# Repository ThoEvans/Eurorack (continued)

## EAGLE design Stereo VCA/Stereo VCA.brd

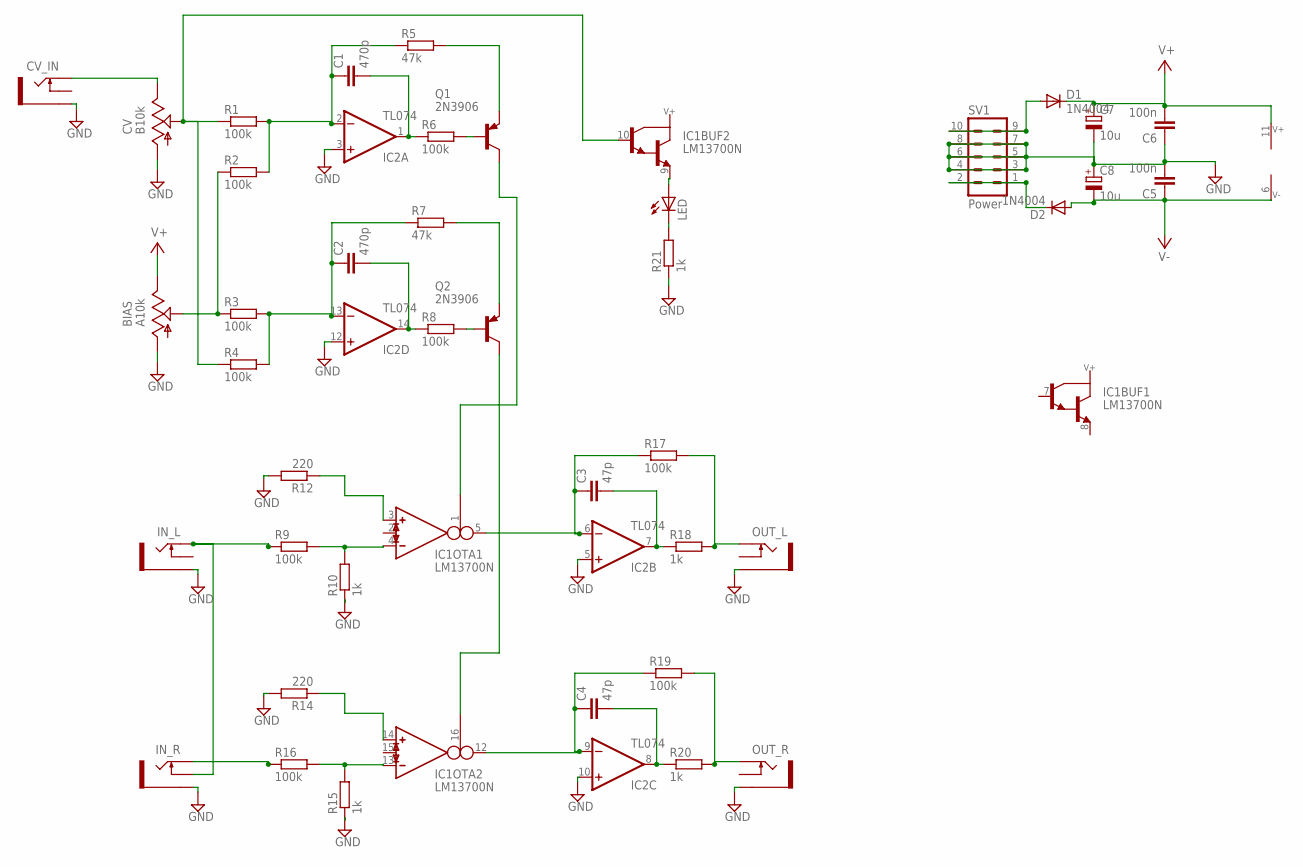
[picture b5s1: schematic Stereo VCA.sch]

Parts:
BIAS: A10k; EVUE
C1, C2: 470p; C050-024X044
C3, C4: 47p; C050-024X044
C5, C6: 100n; C050-024X044
C7, C8: 10u; E3,5-8
CV: B10k; EVUE
CV_IN: PJ302M
D1, D2: 1N4004; DO41-10
IC1: LM13700N; DIL16
IC2: TL074; DIL14
IN_L: PJ302M
IN_R: PJ302M
LED: LED3MM
OUT_L: PJ302M
OUT_R: PJ302M
Q1, Q2: 2N3906; TO92
R1, R2, R3, R4, R6, R8, R9, R16, R17, R19: 100k; 0204/7
R5, R7: 47k; 0204/7
R10, R15, R18, R20, R21: 1k; 0204/7
R12, R14: 220; 0204/7
SV1: Power; EURO_PWR_HEADER_FAT

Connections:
GND: BIAS.1 (A), C5.2, C6.1, C7.-, C8.+, CV.1 (A), CV_IN.GND (SLEEVE), IC2.3 (+IN), IC2.5 (+IN), IC2.10 (+IN), IC2.12 (+IN), IN_L.GND (SLEEVE), IN_R.GND (SLEEVE), OUT_L.GND (SLEEVE), OUT_R.GND (SLEEVE), R10.1, R12.2, R14.2, R15.1, R21.1, SV1.3, SV1.4, SV1.5, SV1.6, SV1.7, SV1.8
unnamed: CV.3 (E), CV_IN.TIP
unnamed: BIAS.2 (S), R2.1, R3.1
unnamed: IC1.9 (E), LED.A
unnamed: C2.1, IC2.13 (-IN), R3.2, R4.2, R7.1
unnamed: C1.2, IC2.1 (OUT), R6.1
unnamed: Q1.2 (B), R6.2
unnamed: Q1.3 (E), R5.2
unnamed: Q2.3 (E), R7.2
unnamed: C2.2, IC2.14 (OUT), R8.1
unnamed: IN_L.TIP, IN_R.SW (SWITCH), R9.1
unnamed: IC1.4 (IN_N), R9.2, R10.2
unnamed: Q2.2 (B), R8.2
unnamed: IC1.3 (IN_P), R12.1
unnamed: C1.1, IC2.2 (-IN), R1.2, R2.2, R5.1
unnamed: IC1.13 (IN_N), R15.2, R16.2
unnamed: IC1.14 (IN_P), R14.1
unnamed: C3.1, IC1.5 (OUT), IC2.6 (-IN), R17.1
unnamed: IC1.1 (I_BIAS), Q1.1 (C)
unnamed: C3.2, IC2.7 (OUT), R18.1
unnamed: OUT_L.TIP, R17.2, R18.2
unnamed: C4.1, IC1.12 (OUT), IC2.9 (-IN), R19.1
unnamed: IC1.16 (I_BIAS), Q2.1 (C)
unnamed: C4.2, IC2.8 (OUT), R20.1
unnamed: OUT_R.TIP, R19.2, R20.2
unnamed: IN_R.TIP, R16.1
unnamed: LED.K (C), R21.2
unnamed: CV.2 (S), IC1.10 (B), R1.1, R4.1
unnamed: D2.C, SV1.1, SV1.2
unnamed: D1.A, SV1.9, SV1.10
V+: BIAS.3 (E), C6.2, C7.+, D1.C, IC1.11 (V+), IC2.4 (V+)
V-: C5.1, C8.-, D2.A, IC1.6 (V-), IC2.11 (V-)

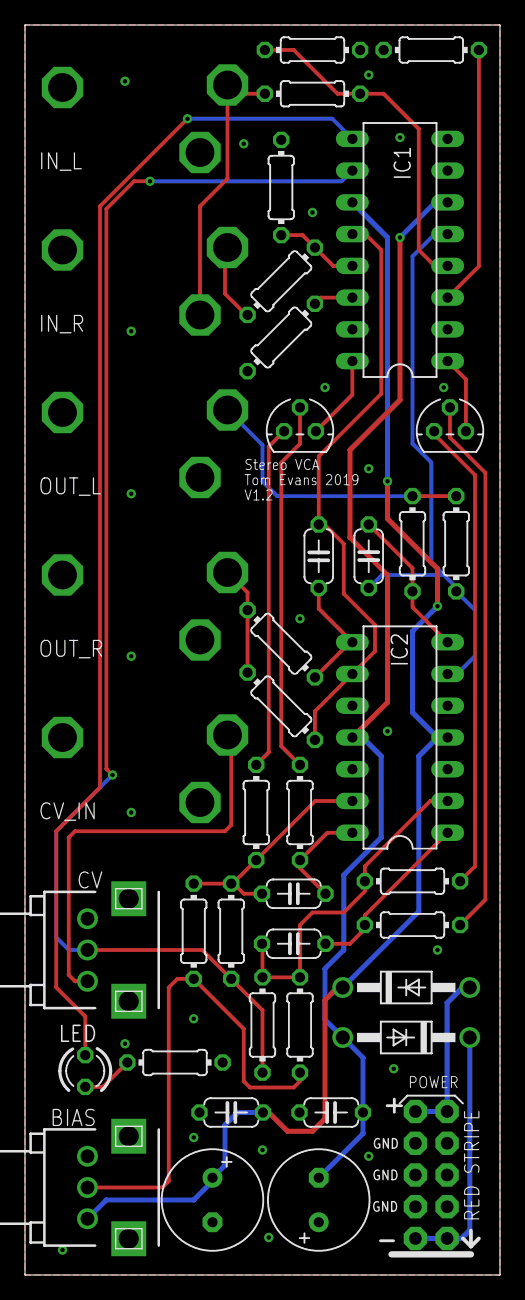
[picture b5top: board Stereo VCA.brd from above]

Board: 2 copper layers, 38.0 x 100.0 mm, 42 parts (0 on the bottom side), 32 nets.

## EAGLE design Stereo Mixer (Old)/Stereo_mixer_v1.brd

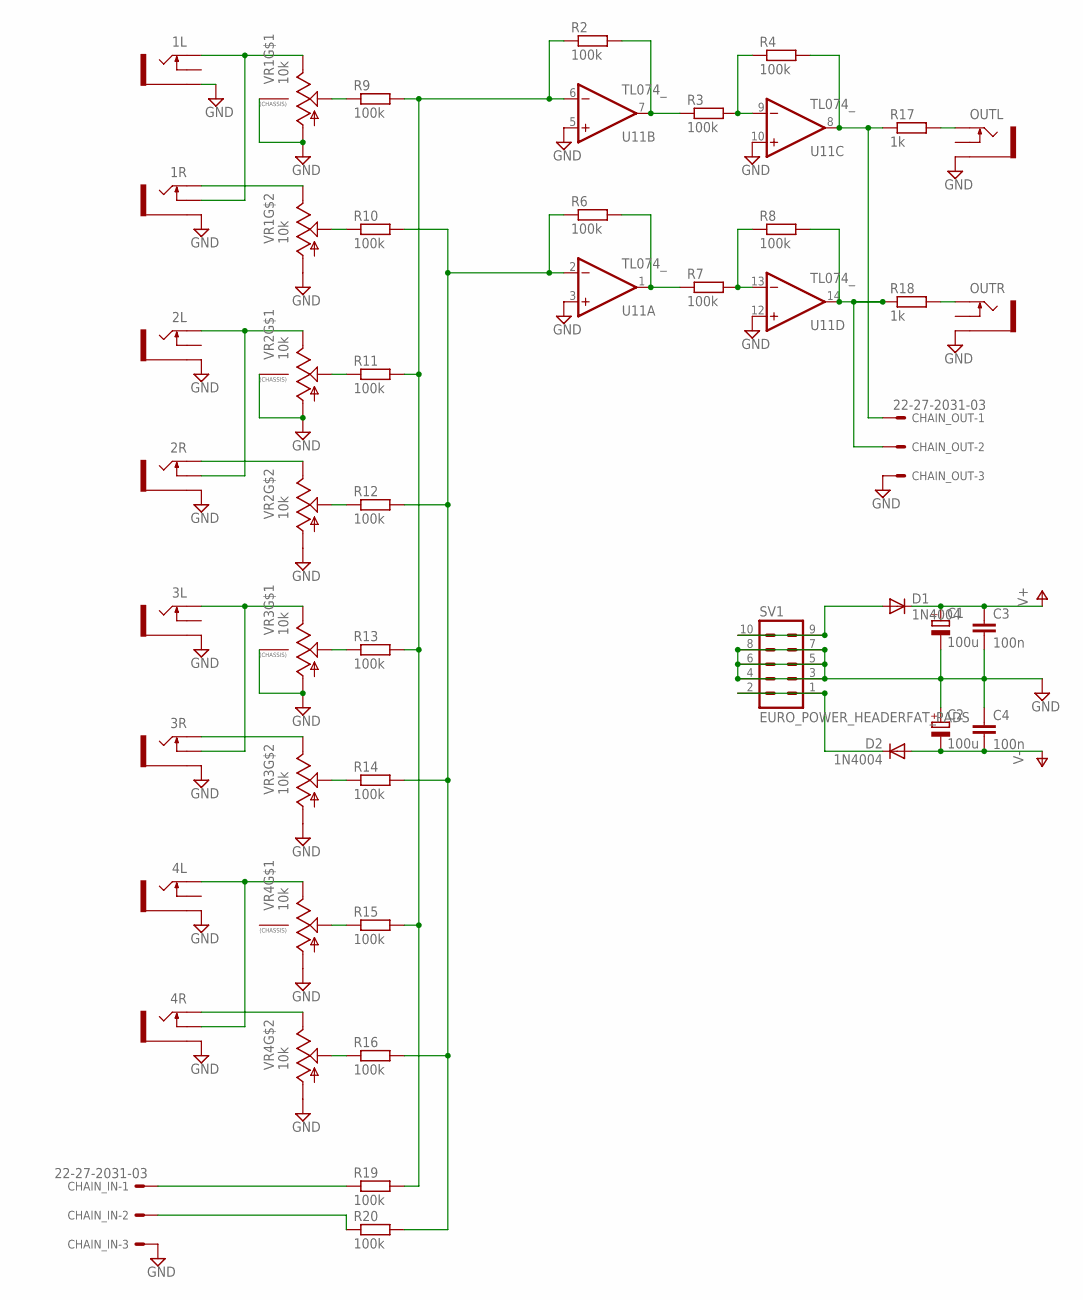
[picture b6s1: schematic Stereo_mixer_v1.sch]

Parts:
1L, 1R, 2L, 2R, 3L, 3R, 4L, 4R: THONKICONNNEW; WQP-PJ301M-12_JACK
C1, C2: 100u; E2,5-6
C3, C4: 100n; C025-024X044
CHAIN_IN: 22-27-2031-03; 6410-03
CHAIN_OUT: 22-27-2031-03; 6410-03
D1, D2: 1N4004; DO41-10
OUTL: THONKICONNNEW; WQP-PJ301M-12_JACK
OUTR: THONKICONNNEW; WQP-PJ301M-12_JACK
R2, R3, R4, R6, R7, R8, R9, R10, R11, R12, R13, R14, R15, R16, R19, R20: 100k; 0207/7
R17, R18: 1k; 0207/7
SV1: EURO_POWER_HEADERFAT_PADS; EURO_PWR_HEADER_FAT
U11: TL074_; DIL14
VR1, VR2, VR3, VR4: 10k; DUAL_9MM_SNAP-IN_POT

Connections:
GND: 1L.P$3_SLEEVE (SLEEVE), 1R.P$3_SLEEVE (SLEEVE), 2L.P$3_SLEEVE (SLEEVE), 2R.P$3_SLEEVE (SLEEVE), 3L.P$3_SLEEVE (SLEEVE), 3R.P$3_SLEEVE (SLEEVE), 4L.P$3_SLEEVE (SLEEVE), 4R.P$3_SLEEVE (SLEEVE), C1.-, C2.+, C3.2, C4.1, CHAIN_IN.3, CHAIN_OUT.3, OUTL.P$3_SLEEVE (SLEEVE), OUTR.P$3_SLEEVE (SLEEVE), SV1.3, SV1.4, SV1.5, SV1.6, SV1.7, SV1.8, U11.3 (+IN), U11.5 (+IN), U11.10 (+IN), U11.12 (+IN), VR1.1 (A), VR1.1B (A), VR1.CHASSIS1, VR1.CHASSIS2, VR2.1 (A), VR2.1B (A), VR2.CHASSIS1, VR2.CHASSIS2, VR3.1 (A), VR3.1B (A), VR3.CHASSIS1, VR3.CHASSIS2, VR4.1 (A), VR4.1B (A)
unnamed: 1L.P$1_TIP (TIP), 1R.P$2_SWITCH (SWITCH), VR1.3 (E)
unnamed: R10.1, VR1.2B (S)
unnamed: R9.1, VR1.2 (S)
unnamed: 1R.P$1_TIP (TIP), VR1.3B (E)
unnamed: 2L.P$1_TIP (TIP), 2R.P$2_SWITCH (SWITCH), VR2.3 (E)
unnamed: D1.A, SV1.9, SV1.10
unnamed: R11.1, VR2.2 (S)
unnamed: 2R.P$1_TIP (TIP), VR2.3B (E)
unnamed: R12.1, VR2.2B (S)
unnamed: 3L.P$1_TIP (TIP), 3R.P$2_SWITCH (SWITCH), VR3.3 (E)
unnamed: R13.1, VR3.2 (S)
unnamed: R14.1, VR3.2B (S)
unnamed: 3R.P$1_TIP (TIP), VR3.3B (E)
unnamed: 4L.P$1_TIP (TIP), 4R.P$2_SWITCH (SWITCH), VR4.3 (E)
unnamed: R15.1, VR4.2 (S)
unnamed: R16.1, VR4.2B (S)
unnamed: 4R.P$1_TIP (TIP), VR4.3B (E)
unnamed: CHAIN_IN.1, R19.1
unnamed: CHAIN_IN.2, R20.1
unnamed: R2.1, R9.2, R11.2, R13.2, R15.2, R19.2, U11.6 (-IN)
unnamed: R6.1, R10.2, R12.2, R14.2, R16.2, R20.2, U11.2 (-IN)
unnamed: R3.2, R4.1, U11.9 (-IN)
unnamed: R7.2, R8.1, U11.13 (-IN)
unnamed: OUTL.P$1_TIP (TIP), R17.2
unnamed: OUTR.P$1_TIP (TIP), R18.2
unnamed: R6.2, R7.1, U11.1 (OUT)
unnamed: CHAIN_OUT.2, R8.2, R18.1, U11.14 (OUT)
unnamed: CHAIN_OUT.1, R4.2, R17.1, U11.8 (OUT)
unnamed: R2.2, R3.1, U11.7 (OUT)
unnamed: D2.C, SV1.1, SV1.2
V+: C1.+, C3.1, D1.C, U11.4 (V+)
V-: C2.-, C4.2, D2.A, U11.11 (V-)

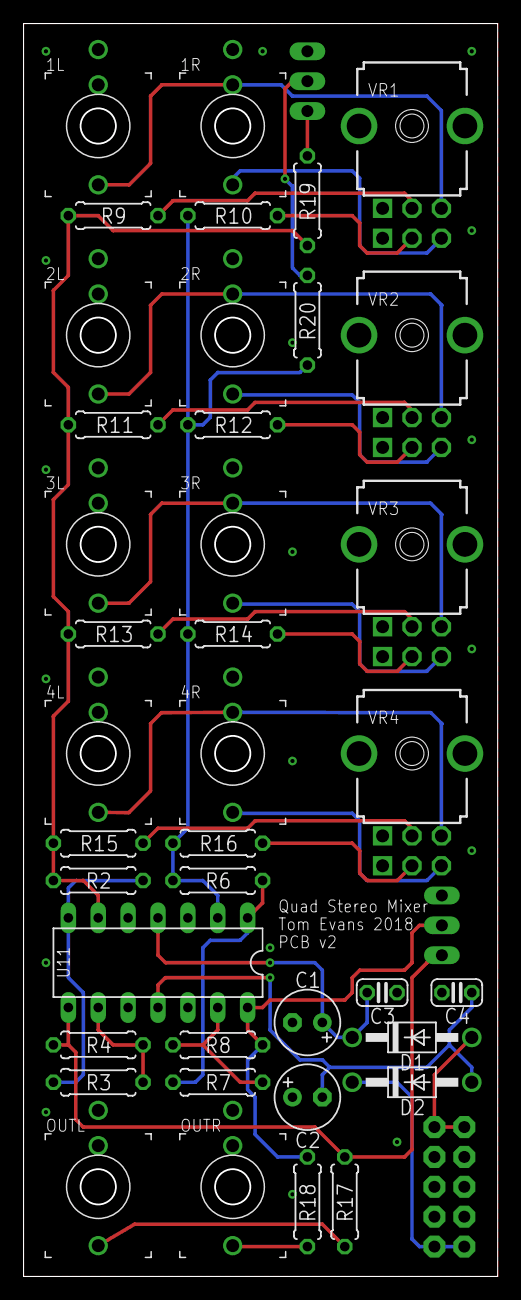
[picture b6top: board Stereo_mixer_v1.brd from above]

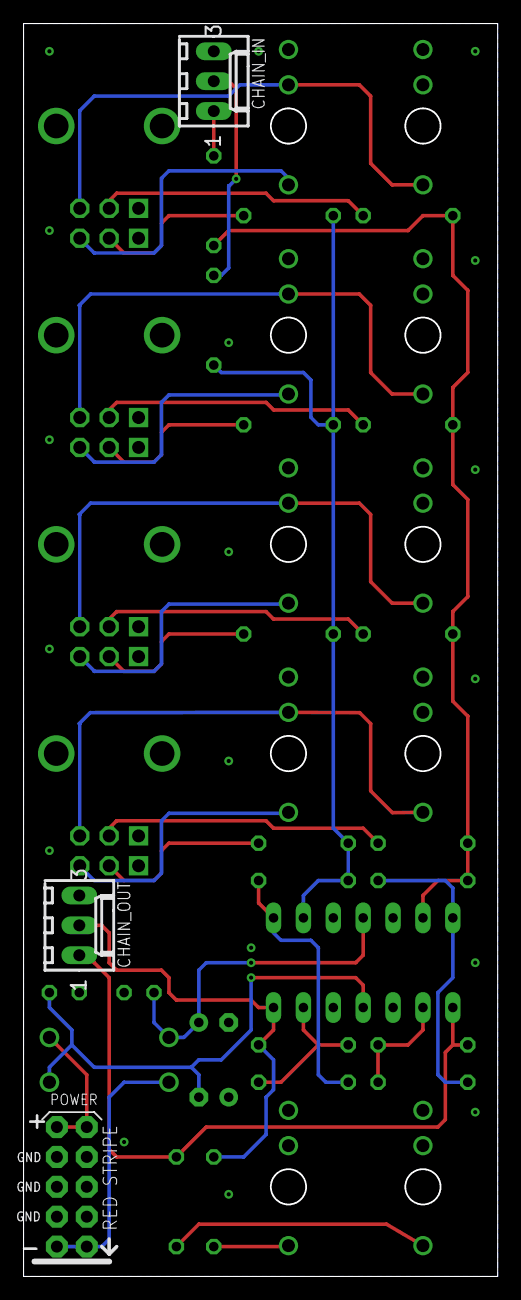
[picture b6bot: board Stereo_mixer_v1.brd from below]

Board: 2 copper layers, 40.3 x 106.5 mm, 42 parts (3 on the bottom side), 33 nets.

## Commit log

2019-01-26 Added BoM
    Bill of Materials in Zip folder,
    Added a hole in the PCBs for a hex standoff and screws,
    Also Normalized FCV1 to FCV2.
2019-01-26 Added BoM + PCB screw hole
    Also Normalized FCV1 to FCV2 via switching jacks.
2019-02-11 Work in progress...
    Gate Addressed Voltage Selector
2019-02-17 Test
2019-02-17 Updated Mixer layout
2019-02-17 Stereo Mixer V1
2019-02-17 Updated file structure
2019-04-17 Create LICENSE
2019-04-17 Add files via upload
    Minor resistor value change
2019-04-17 Minor Value Changes
    33k resistors -> 30k resistors
    470nF film caps -> 1uF film caps
2019-09-15 Updated panel graphics
2020-04-19 Add files via upload
    7 Resistors changed
2020-04-19 Rev 4
2020-11-25 Prototype
